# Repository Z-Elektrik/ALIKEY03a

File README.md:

## ALIKEY03a - Tlacidlova doska 1x3  r.00, 2024.10.25

ALIKEY03a - TOP:

ALIKEY03a - BOTTOM:

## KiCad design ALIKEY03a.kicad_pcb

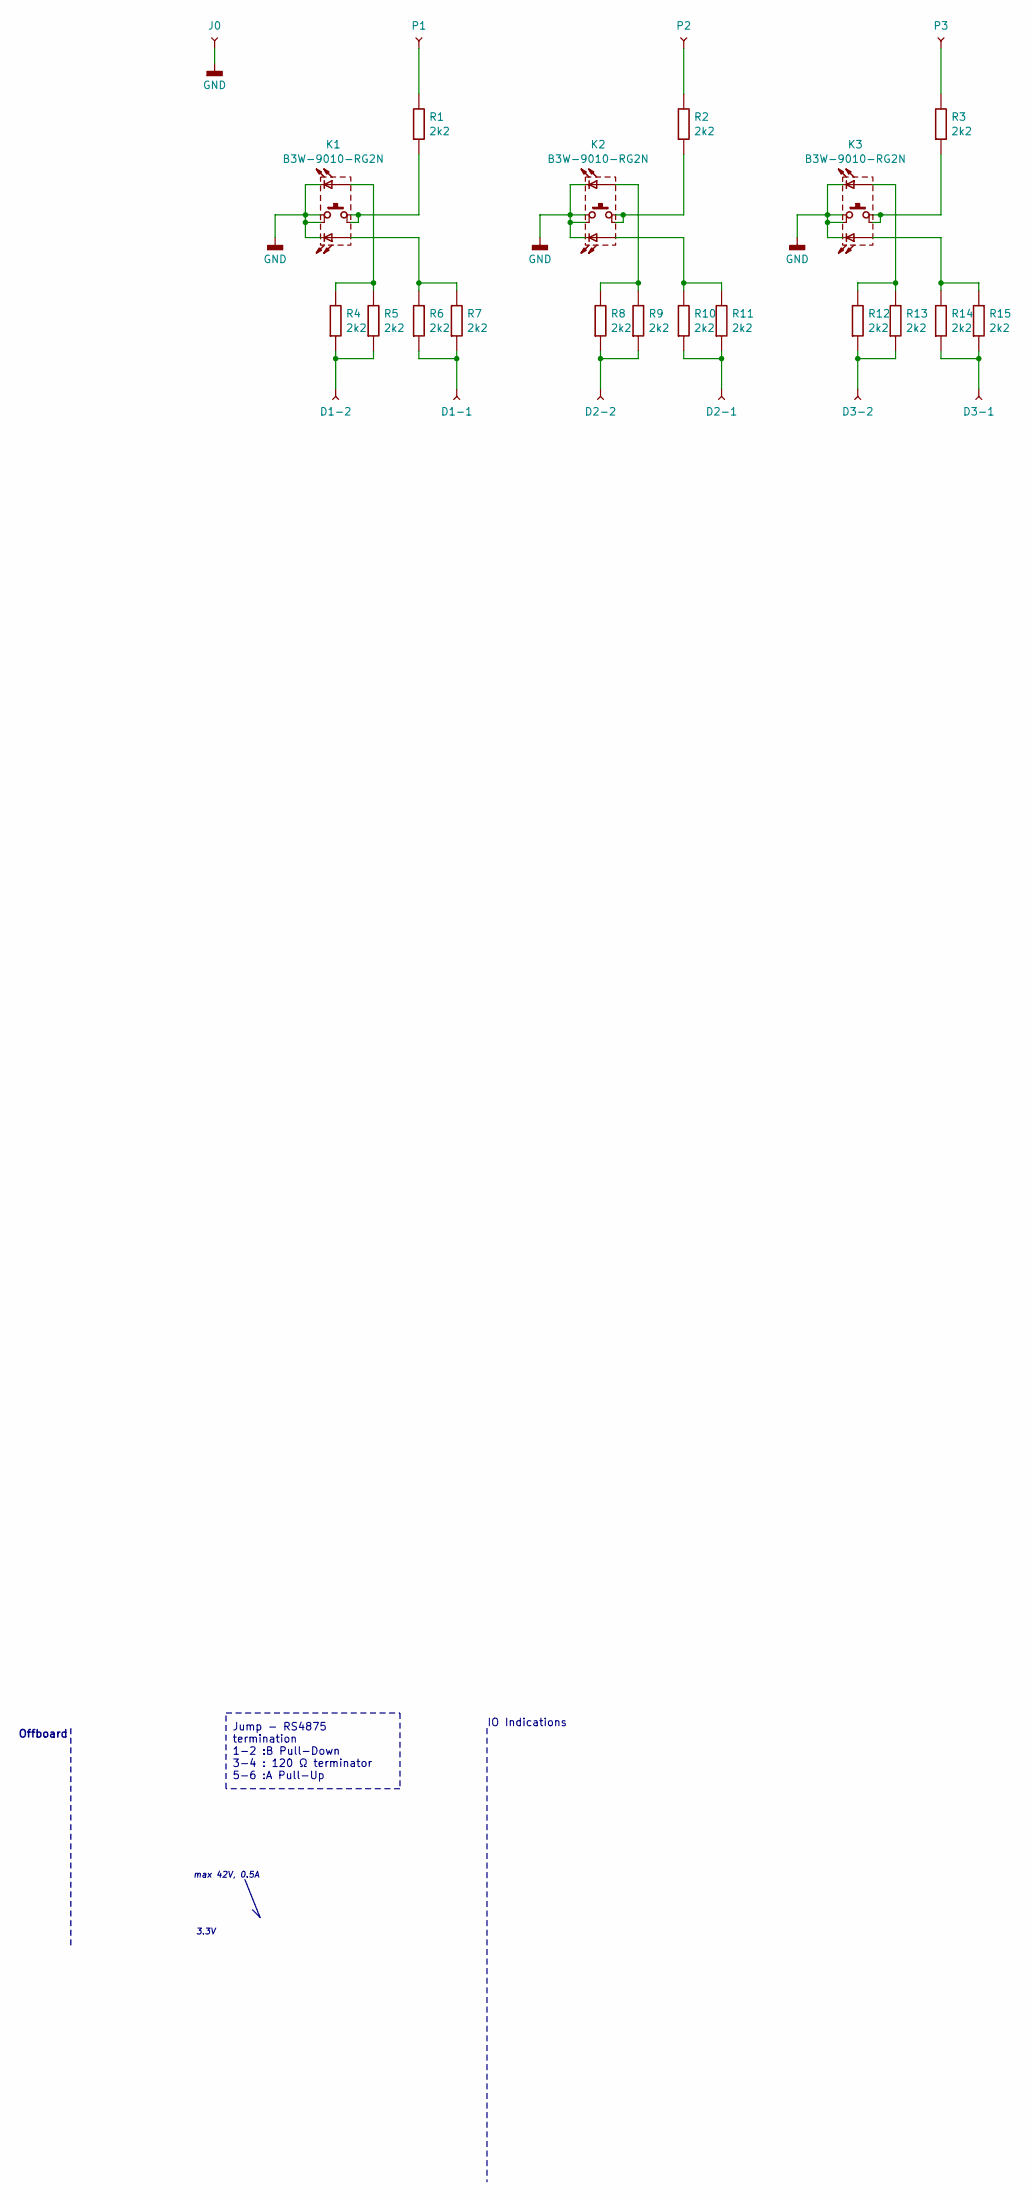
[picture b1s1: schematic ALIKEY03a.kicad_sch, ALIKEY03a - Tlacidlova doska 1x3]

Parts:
D1-1, D1-2, D2-1, D2-2, D3-1, D3-2: TestPoint; SMD_PAD_R200_508R50
J0: TestPoint; SMD_PAD_R254_508R50
K1, K2, K3: B3W-9010-RG2N; B3W-90xx-x2xN_Omron; MPN B3W-9010-RG2N
P1, P2, P3: TestPoint; SMD_PAD_R254_508R50
R1, R2, R3, R4, R5, R6, R7, R8, R9, R10, R11, R12, R13, R14, R15: 2k2; RESC3116X65N_1206

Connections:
GND_Bar: J0.1, K1.1, K1.2, K1.C1, K1.C2, K2.1, K2.2, K2.C1, K2.C2, K3.1, K3.2, K3.C1, K3.C2
unnamed: D1-1.1, R6.1, R7.1
unnamed: D1-2.1, R4.1, R5.1
unnamed: D2-1.1, R10.1, R11.1
unnamed: D2-2.1, R8.1, R9.1
unnamed: D3-1.1, R14.1, R15.1
unnamed: D3-2.1, R12.1, R13.1
unnamed: K1.3, K1.4, R1.1
unnamed: K1.A1, R6.2, R7.2
unnamed: K1.A2, R4.2, R5.2
unnamed: K2.3, K2.4, R2.1
unnamed: K2.A1, R10.2, R11.2
unnamed: K2.A2, R8.2, R9.2
unnamed: K3.3, K3.4, R3.1
unnamed: K3.A1, R14.2, R15.2
unnamed: K3.A2, R12.2, R13.2
unnamed: P1.1, R1.2
unnamed: P2.1, R2.2
unnamed: P3.1, R3.2

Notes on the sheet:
Jump - RS4875 termination 1-2 :B Pull-Down 3-4 : 120 Ω terminator 5-6 :A Pull-Up
max 42V, 0.5A
Offboard
3.3V
IO Indications

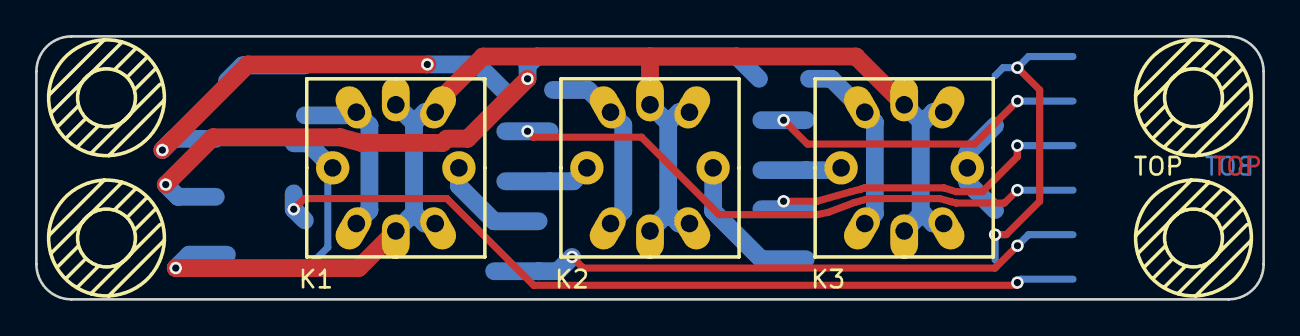
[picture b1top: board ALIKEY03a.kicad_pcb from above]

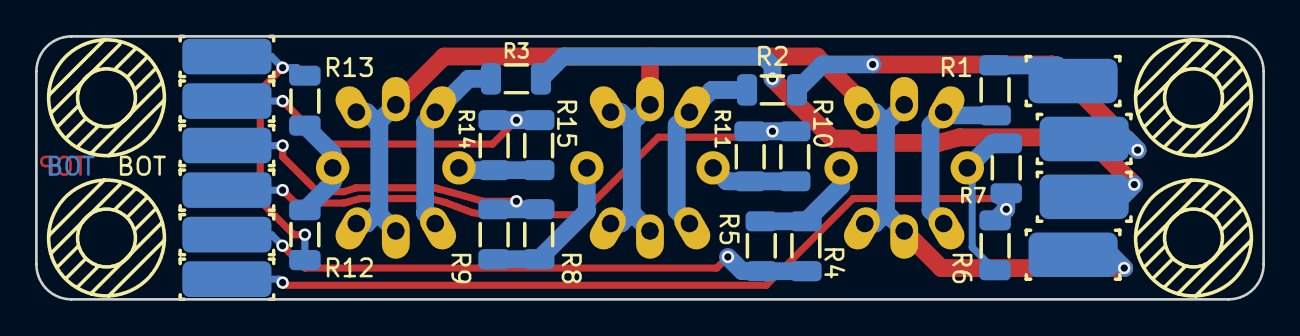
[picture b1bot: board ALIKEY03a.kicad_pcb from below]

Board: 2 copper layers, 70.0 x 15.0 mm, 28 parts (25 on the bottom side), 19 nets.

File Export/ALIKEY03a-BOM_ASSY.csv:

"#","Technology","Reference","Z-SYSCODE","Qty","Value","Footprint"
"1","SMD","R1,R2,R3,R4,R5,R6,R7,R8,R9,R10,R11,R12,R13,R14,R15","3569","15","2k2","SMD_Resistor_Generic:RESC3116X65N_1206"
"2","THD","K1,K2,K3","","3","B3W-9010-RG2N","THD_Switch_Omron:B3W-90xx-x2xN_Omron"

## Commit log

2024-10-23 Updated model wo Optimalization
2024-10-25 Final version
